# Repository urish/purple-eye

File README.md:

purple-eye
==========

> A web-bluetooth controlled 3d-printed dancing robot

## Prerequisites

The Web Interface uses [Web Bluetooth](https://medium.com/@urish/start-building-with-web-bluetooth-and-progressive-web-apps-6534835959a6) and is available on Chrome on the following platforms:

* Android 6.0 or newer
* Mac OS X 10.10 or newer
* Recent Linux ([see here for details](https://acassis.wordpress.com/2016/06/28/how-to-get-chrome-web-bluetooth-working-on-linux/))
* Windows 10 (Chrome Canary only)
* Chrome OS

[Online Web Interface](https://urish.github.io/purple-eye/)

## Hardware

➡ [Read how to make your own "Purple Eye" robot](https://medium.com/@urish/making-purple-eye-diy-dancing-robot-fa03d0f658e2#.q7gzas4cq)

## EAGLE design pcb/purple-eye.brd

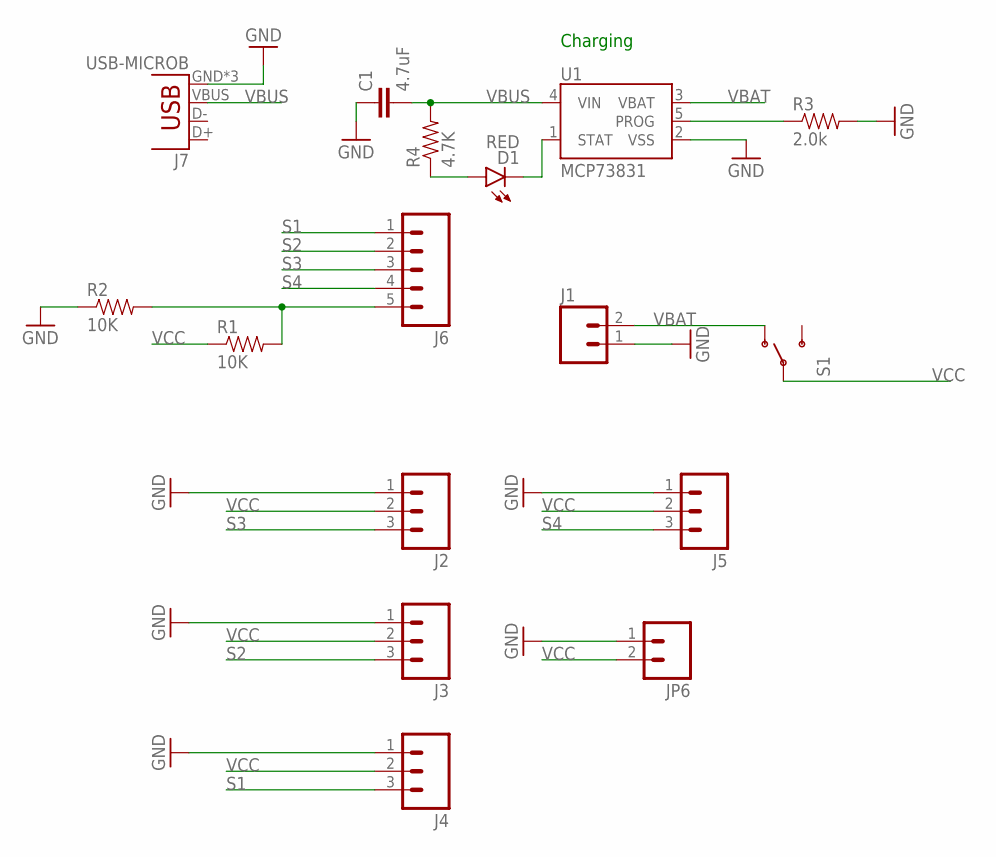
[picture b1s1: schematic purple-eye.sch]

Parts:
C1: 4.7uF; 0603-CAP
D1: RED; LED-0603
J1: M02JST-PTH-2; JST-2-PTH
J2, J3, J4, J5: M03LOCK; 1X03_LOCK
J6: M05LOCK; 1X05_LOCK
J7: USB-MICROB
JP6: M02LOCK; 1X02_LOCK
R1, R2: 10K; 0603-RES
R3: 2.0k; 0603-RES
R4: 4.7K; 0603-RES
S1: SWITCH-SPDTPTH_LOCK; SWITCH-SPDT_LOCK.007S
U1: MCP73831; SOT23-5

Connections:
GND: C1.1, J1.1, J2.1, J3.1, J4.1, J5.1, J7.GND, J7.MT1 (GND), J7.MT2 (GND), JP6.1, R2.1, R3.2, U1.2 (VSS)
unnamed: J6.5, R1.2, R2.2
unnamed: R3.1, U1.5 (PROG)
unnamed: D1.A, R4.1
unnamed: D1.C, U1.1 (STAT)
S1: J4.3, J6.1
S2: J3.3, J6.2
S3: J2.3, J6.3
S4: J5.3, J6.4
VBAT: J1.2, S1.1 (O), U1.3 (VBAT)
VBUS: C1.2, J7.VBUS, R4.2, U1.4 (VIN)
VCC: J2.2, J3.2, J4.2, J5.2, JP6.2, R1.1, S1.2

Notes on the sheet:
Charging

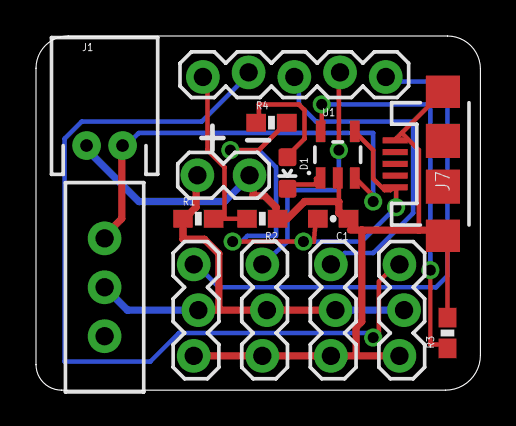
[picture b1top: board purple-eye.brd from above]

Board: 2 copper layers, 24.7 x 19.7 mm, 16 parts (0 on the bottom side), 12 nets.

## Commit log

2016-05-06 deploy demo to gh-pages
2016-05-06 add twitter / github links
2016-05-06 css fix
2016-05-15 change BLE robot name to PurpleEye
2016-05-15 don't allow shimmy and dance at the same time
2016-05-15 implement a rest command
2016-05-20 add Physical Web (Eddystone) beacon to the firmware
2016-05-20 add LiPo battery to list of hardware components
2016-05-20 s/connectGATT/gatt.connect/g
2016-05-30 add robot image
2016-06-14 Add Battery Service to Firmware
    adds support for measuring the remaining battery percentage by exposing a BLE Battery Service
2016-06-19 rename blue-eye -> purple-eye
2016-06-20 Display battery level indication
2016-06-20 Nit: s/Charasteristic/Characteristic
2016-07-10 Add Power Circuit PCB
2016-08-10 Port firmware to the BLE Nano board
2016-08-12 Fixes in the BLE Nano firmware
    1. Implement "REST" mode (turn servos off)
    2. Correct battery level reporting
    3. Turn LED off to conserve power
2016-08-14 Improve servo control accuracy on the nRF51
    The new servo code works in conjuction with the softdevice firmware to make sure servo timings are accurate on the nRF51822 chip.
2016-08-26 Add Web Bluetooth Origin Trial token
2016-09-29 Update Web Bluetooth Origin Trial token
2016-10-22 additional improvements to nrf51 servo code
2016-10-22 adjust dance/shimmy timings for the new nrf51 firmware
2016-10-29 Update the Prerequisites section in README
2016-11-03 Remove the "Updating servos..." debug print
    Apparently, it messes up the servo control timing
2016-11-04 Add IMU sensor support
2016-12-08 Visualize robot orientation
    Using IMU data + three.js
2016-12-12 Add optional Gyro sensor
2016-12-12 Add persistence for servo offsets
    We use nrf's fstorage for storing 4 bytes, each contains offset correction for one of the servos
2016-12-21 chore: update origin trial token
2016-12-21 add 3d model of the robot head (blender)
2016-12-21 feat(firmware): sound card integration
2017-01-21 reduce advertisement packet size
2017-01-22 Make the robot dance when ng-beacon is around
2017-04-19 feat: add charging circuit
2018-08-26 refactor: start rewriting PurpleEye firmware in JS
    using Espruino
2018-08-26 docs: update list of supported platforms in README
2018-08-26 refactor: finish rewriting the firmware in JS
2018-12-29 cleanup(firmware): remove physical web stuff
    Physical Web is now deprecated :-(
2018-12-29 fix(firmware): Improve movement range
2019-01-11 feat: new PCB (designed with EasyEDA)
    https://easyeda.com/uri_6323/purple-eye

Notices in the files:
parts and their libraries:
SparkFun-Connectors: Licensing: Creative Commons ShareAlike 4.0 International - https://creativecommons.org/licenses/by-sa/4.0
